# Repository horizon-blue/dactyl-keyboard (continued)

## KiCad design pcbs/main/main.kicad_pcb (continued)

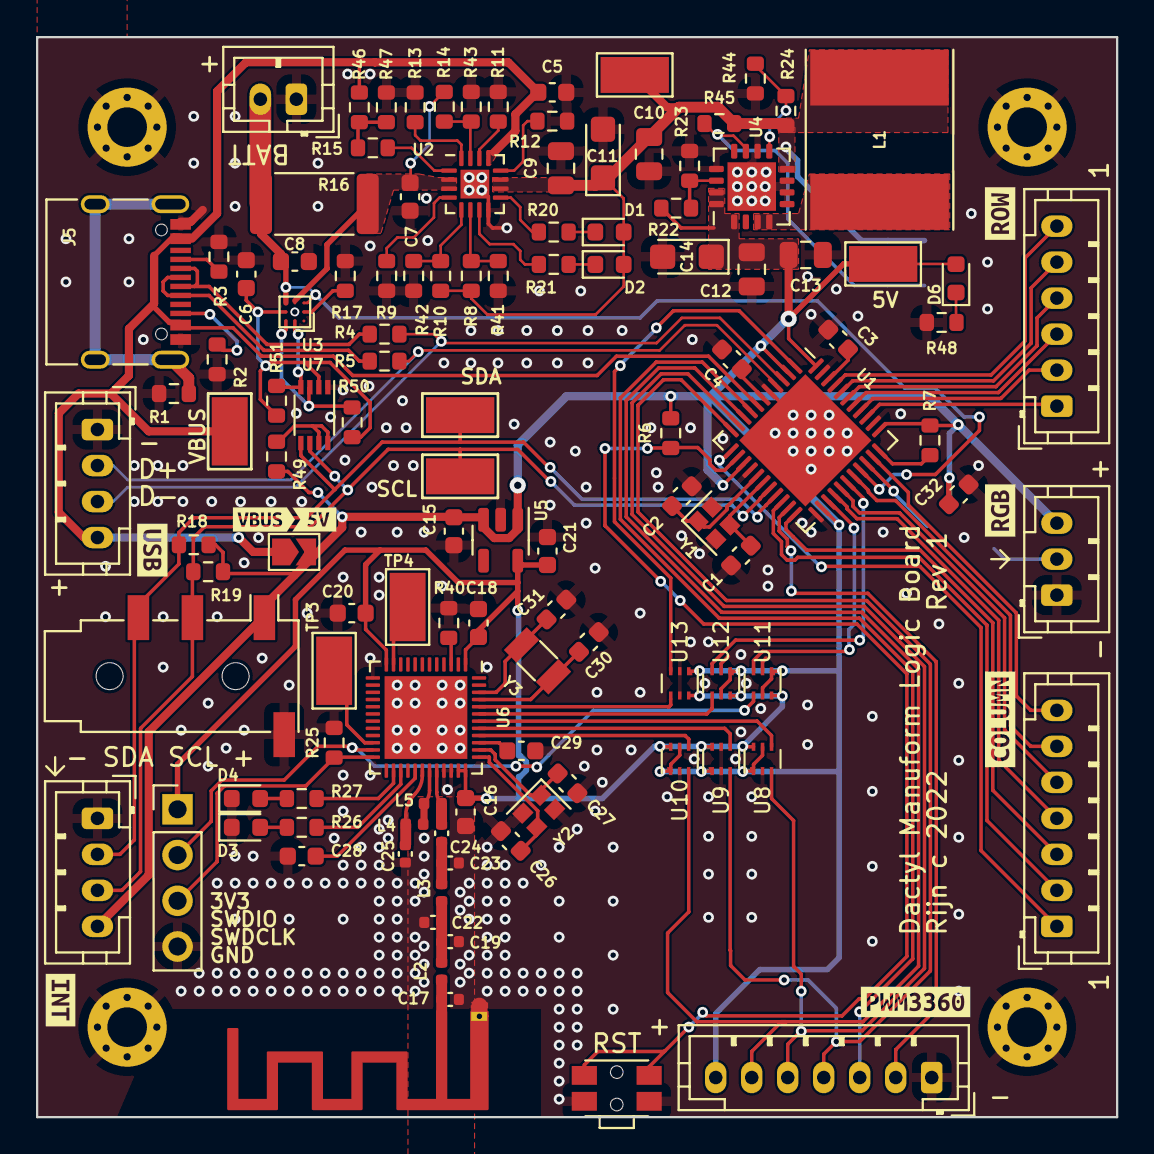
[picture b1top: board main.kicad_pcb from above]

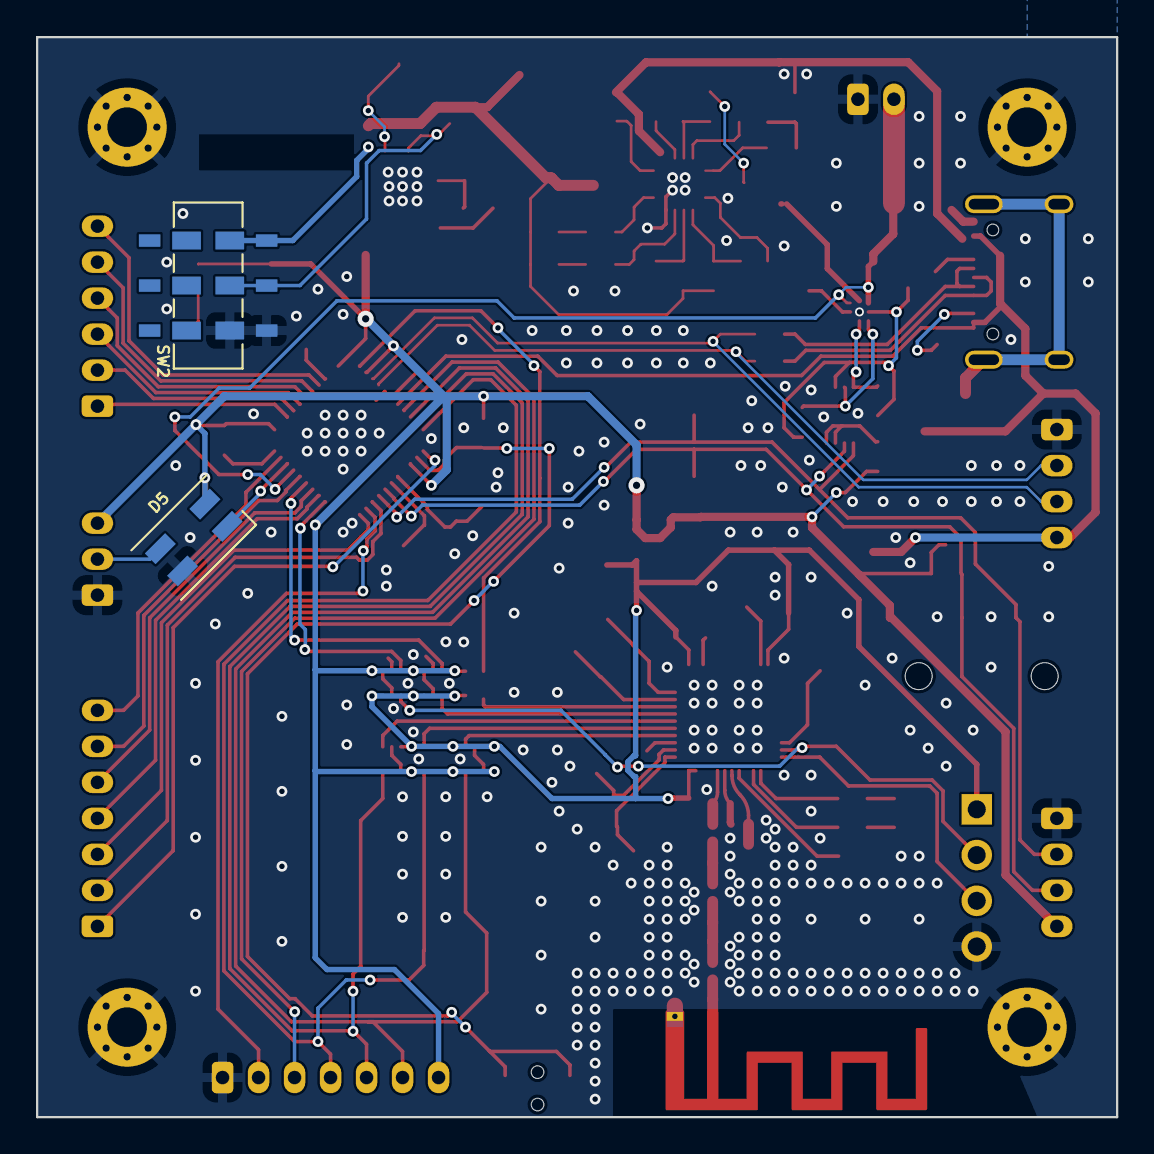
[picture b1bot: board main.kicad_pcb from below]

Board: 2 copper layers, 60.0 x 60.0 mm, 131 parts (2 on the bottom side), 94 nets.

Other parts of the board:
kibuzzard-62C9005A: G***; kibuzzard-62C9005A
kibuzzard-62C9006A: G***; kibuzzard-62C9006A
kibuzzard-62C9009F: G***; kibuzzard-62C9009F
kibuzzard-62C90078: G***; kibuzzard-62C90078
kibuzzard-62C90085: G***; kibuzzard-62C90085
kibuzzard-62C90092: G***; kibuzzard-62C90092
kibuzzard-62F083BB: G***; kibuzzard-62F083BB
kibuzzard-62F083D5: G***; kibuzzard-62F083D5

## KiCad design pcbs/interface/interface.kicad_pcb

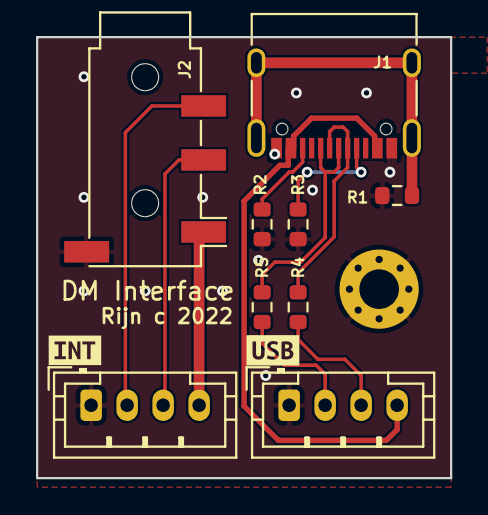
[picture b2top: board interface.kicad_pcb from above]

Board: 4 copper layers, 23.0 x 24.5 mm, 12 parts (0 on the bottom side), 12 nets.

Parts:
H1: MountingHole_Pad; MountingHole_2.2mm_M2_Pad_Via
J1: USB_C_Receptacle_USB2.0; USB_C_Receptacle_XKB_U262-16XN-4BVC11
J2: AudioJack4_Ground; Jack_3.5mm_PJ320D_Horizontal
J3, J4: Conn_01x04_Female; JST_PH_B4B-PH-K_1x04_P2.00mm_Vertical
R1: 0; R_0603_1608Metric
R2, R3: 5.1K; R_0603_1608Metric
R4, R5: 22; R_0603_1608Metric
kibuzzard-62C8FF7E: G***; kibuzzard-62C8FF7E
kibuzzard-62C8FF78: G***; kibuzzard-62C8FF78

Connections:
+5V: J2.T, J3.4
/D+: J4.2, R5.2
/D-: J4.3, R4.2
/SCL: J2.R1, J3.3
/SDA: J2.R2, J3.2
GND: H1.1, J1.A1 (GND), J1.A12 (GND), J1.B1 (GND), J1.B12 (GND), J2.S, J3.1, J4.1, R1.2, R2.1, R3.1
unnamed: J1.A5 (CC1), R3.2
unnamed: J1.A6 (D+), J1.B6 (D+), R5.1
unnamed: J1.A7 (D-), J1.B7 (D-), R4.1
unnamed: J1.B5 (CC2), R2.2
unnamed: J1.S1 (SHIELD), R1.1
VBUS: J1.A4 (VBUS), J1.A9 (VBUS), J1.B4 (VBUS), J1.B9 (VBUS), J4.4

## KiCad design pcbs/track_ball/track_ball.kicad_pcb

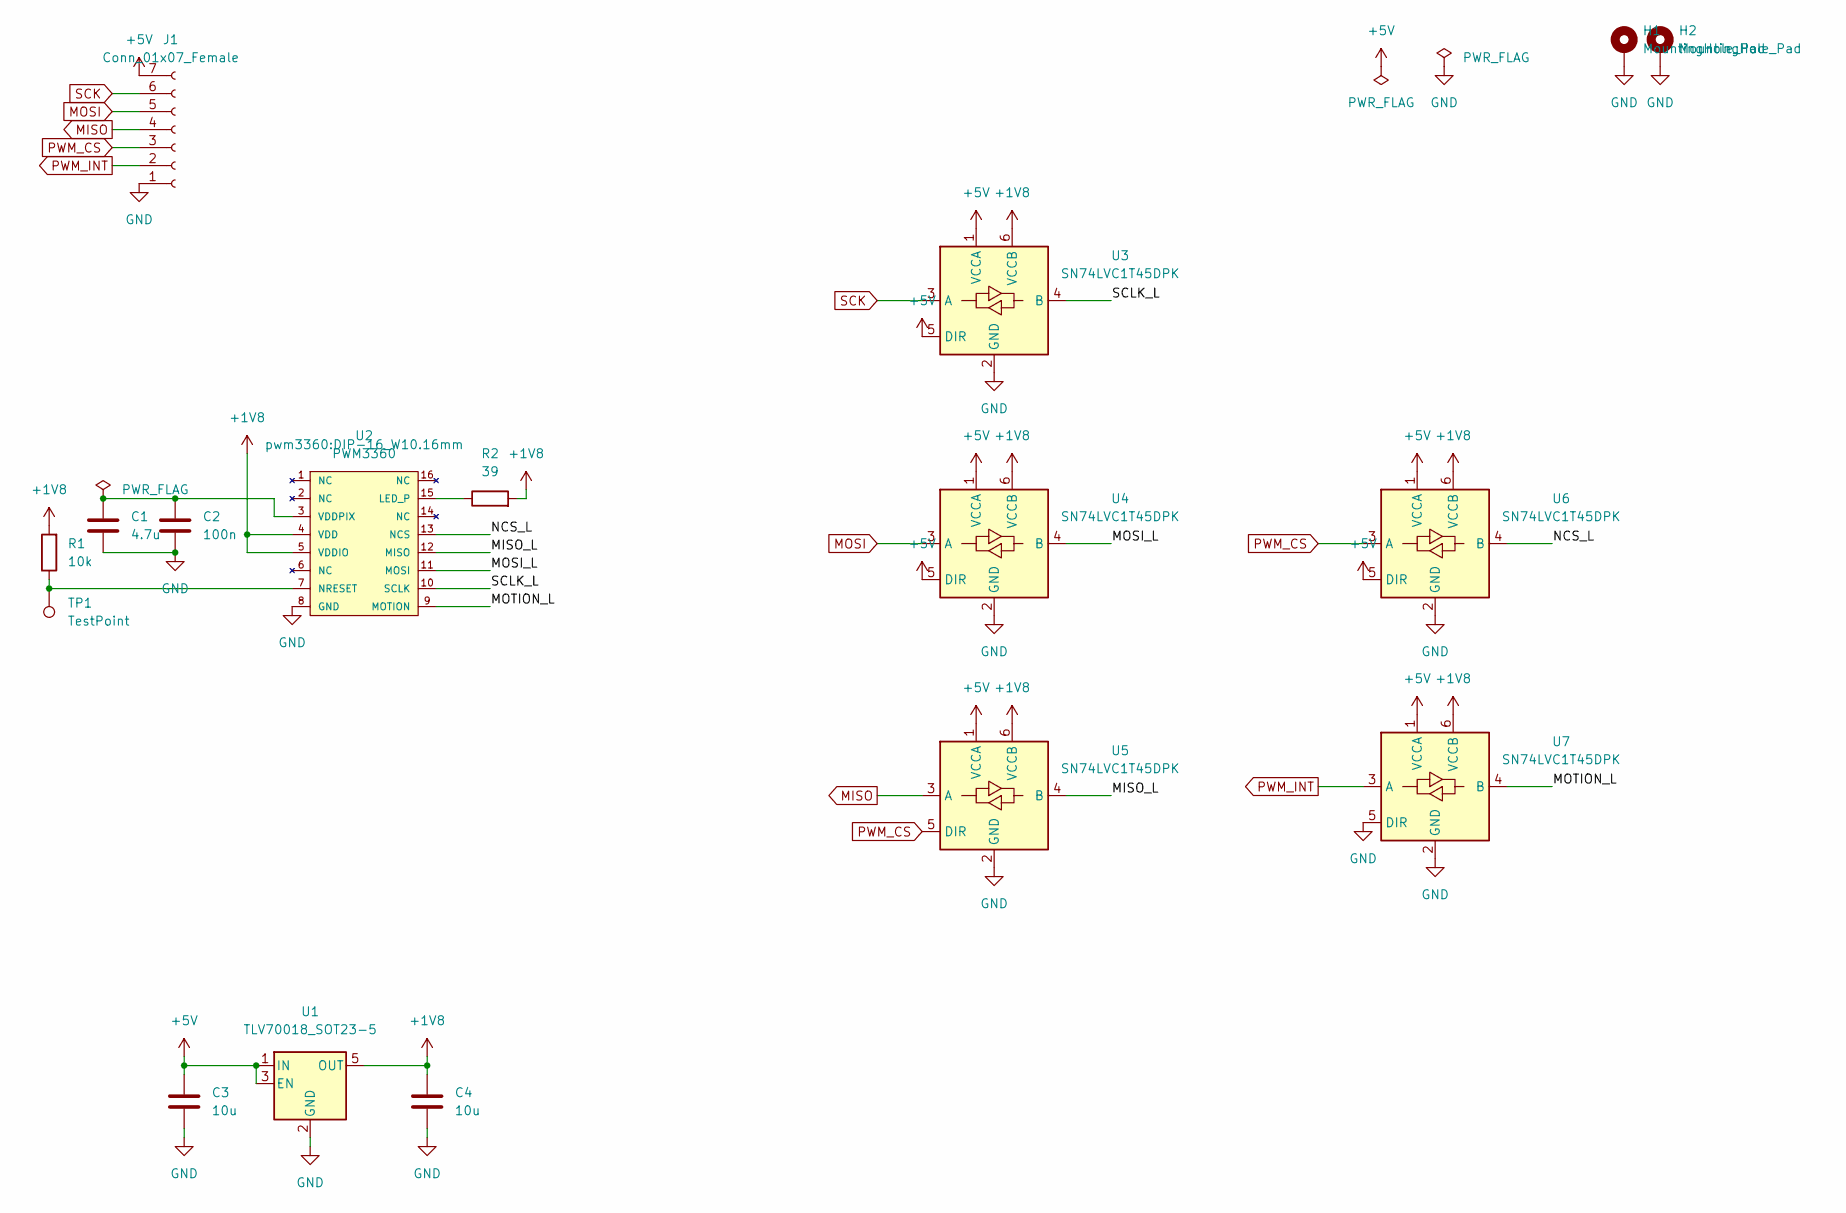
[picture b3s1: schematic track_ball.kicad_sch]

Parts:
C1: 4.7u; C_0603_1608Metric
C2: 100n; C_0603_1608Metric
C3, C4: 10u; C_0603_1608Metric
H1, H2: MountingHole_Pad; MountingHole_2.2mm_M2_Pad_Via
J1: Conn_01x07_Female; JST_PH_B7B-PH-K_1x07_P2.00mm_Vertical
R1: 10k; R_0603_1608Metric
R2: 39; R_0603_1608Metric
TP1: TestPoint; TestPoint_Pad_D1.5mm
U1: TLV70018_SOT23-5; SOT-23-5
U2: PWM3360; DIP-16_W10.16mm
U3, U4, U5, U6, U7: SN74LVC1T45DPK; USON-6

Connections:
+1V8: C4.1, R1.2, R2.2, U1.5 (OUT), U2.4 (VDD), U2.5 (VDDIO), U3.6 (VCCB), U4.6 (VCCB), U5.6 (VCCB), U6.6 (VCCB), U7.6 (VCCB)
+5V: C3.1, J1.7, U1.1 (IN), U1.3 (EN), U3.1 (VCCA), U3.5 (DIR), U4.1 (VCCA), U4.5 (DIR), U5.1 (VCCA), U6.1 (VCCA), U6.5 (DIR), U7.1 (VCCA)
/MISO_L: U2.12 (MISO), U5.4 (B)
/MOSI_L: U2.11 (MOSI), U4.4 (B)
/MOTION_L: U2.9 (MOTION), U7.4 (B)
/NCS_L: U2.13 (NCS), U6.4 (B)
/SCLK_L: U2.10 (SCLK), U3.4 (B)
GND: C1.2, C2.2, C3.2, C4.2, H1.1, H2.1, J1.1, U1.2 (GND), U2.8 (GND), U3.2 (GND), U4.2 (GND), U5.2 (GND), U6.2 (GND), U7.2 (GND), U7.5 (DIR)
MISO: J1.4, U5.3 (A)
MOSI: J1.5, U4.3 (A)
unnamed: C1.1, C2.1, U2.3 (VDDPIX)
unnamed: R1.1, TP1.1, U2.7 (NRESET)
unnamed: R2.1, U2.15 (LED_P)
PWM_CS: J1.3, U5.5 (DIR), U6.3 (A)
PWM_INT: J1.2, U7.3 (A)
SCK: J1.6, U3.3 (A)

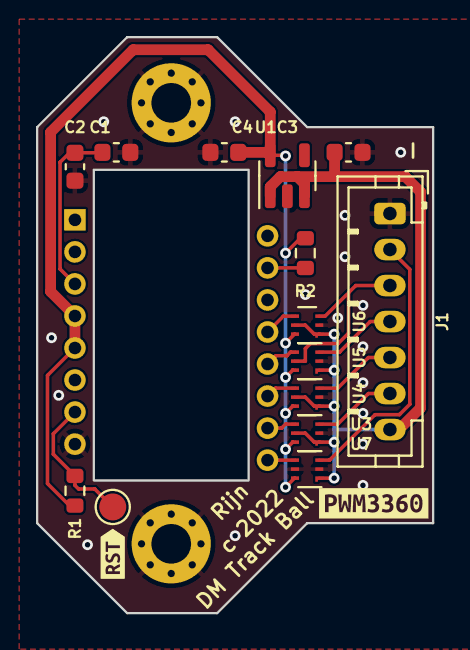
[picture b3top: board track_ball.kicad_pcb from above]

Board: 4 copper layers, 22.0 x 32.0 mm, 19 parts (0 on the bottom side), 16 nets.

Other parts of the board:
kibuzzard-62C9E1CF: G***; kibuzzard-62C9E1CF
kibuzzard-62C9E26A: G***; kibuzzard-62C9E26A

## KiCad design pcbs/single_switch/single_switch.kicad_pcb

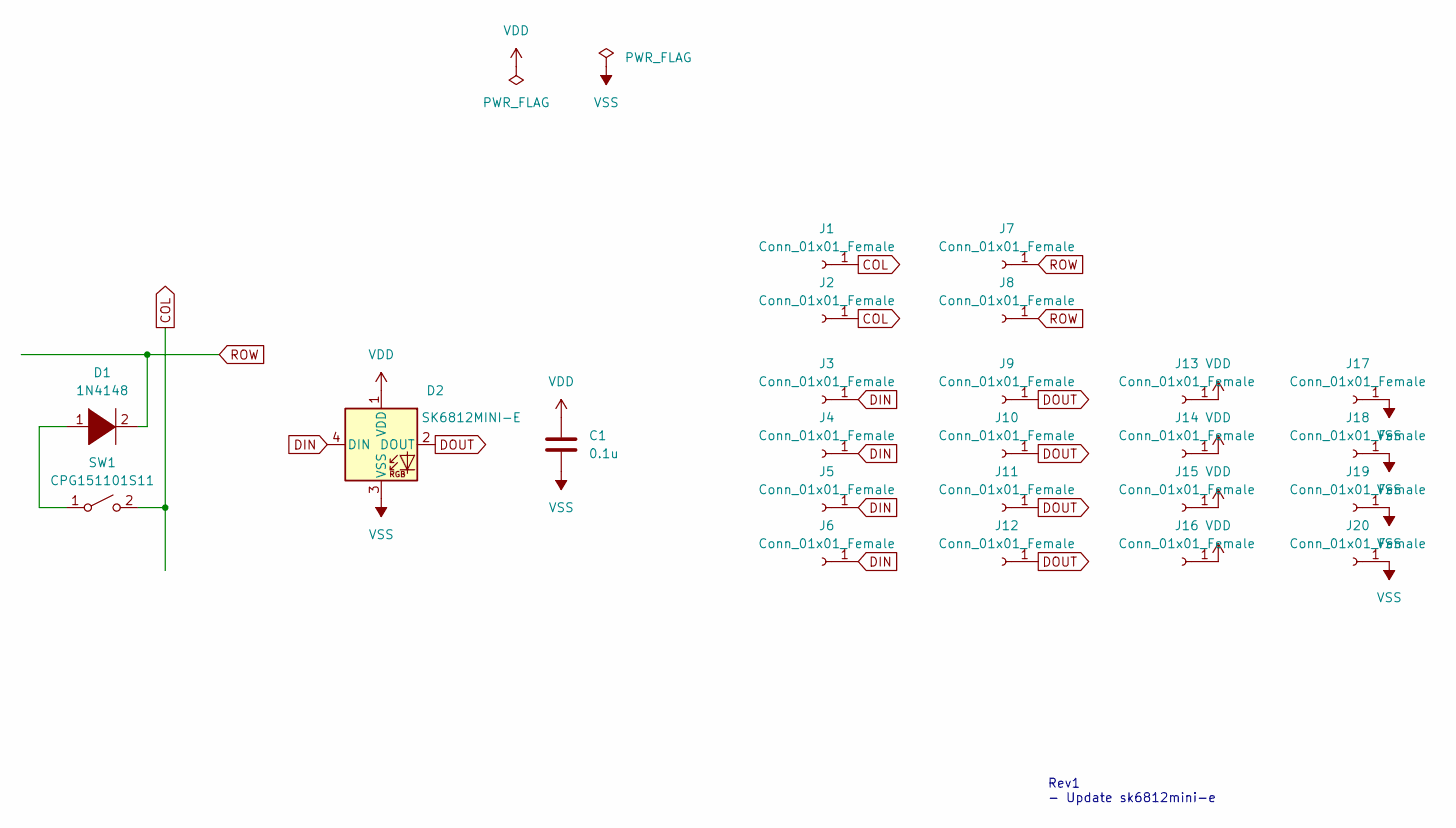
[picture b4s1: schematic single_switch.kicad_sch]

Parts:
C1: 0.1u; C_0603_1608Metric
D1: 1N4148; D_SOD-123
D2: SK6812MINI-E; MX_SK6812MINI-E_REV
J1, J2, J3, J4, J5, J6, J7, J8, J9, J10, J11, J12, J13, J14, J15, J16, J17, J18, J19, J20: Conn_01x01_Female; PinSocket_1x01_P2.00mm_Vertical
SW1: CPG151101S11; Kailh_MX_Socket

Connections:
COL: J1.1, J2.1, SW1.2 (B)
DIN: D2.4 (DIN), J3.1, J4.1, J5.1, J6.1
DOUT: D2.2 (DOUT), J9.1, J10.1, J11.1, J12.1
unnamed: D1.1 (K), SW1.1 (A)
ROW: D1.2 (A), J7.1, J8.1
VDD: C1.1, D2.1 (VDD), J13.1, J14.1, J15.1, J16.1
VSS: C1.2, D2.3 (VSS), J17.1, J18.1, J19.1, J20.1

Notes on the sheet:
Rev1 - Update sk6812mini-e

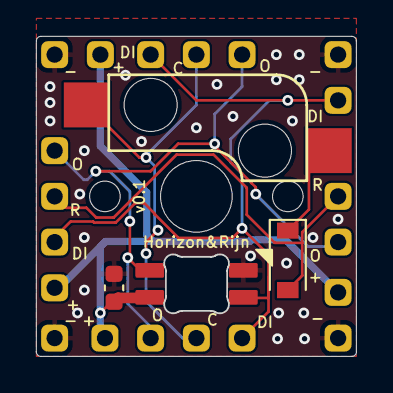
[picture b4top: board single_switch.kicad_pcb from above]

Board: 4 copper layers, 17.8 x 17.8 mm, 24 parts (1 on the bottom side), 7 nets.

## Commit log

2021-10-21 brad_dolph changes
2021-10-22 In the ballpark for customer
2021-10-28 Column tweaking
2021-11-06 Moving workflow setup out of general repo
2021-11-21 Filename fix
2021-11-22 Wilder cluster tweaks, needs more work, smoothing, connect to walls not just corners of key holes.
    Added --save_path argument to customize save paths on local system without dirtying json with local paths.
2021-11-26 Cylinders present for each keyhole
2021-11-30 Initial support branching test
2021-12-01 Supports in a ballpark and exporting separately for right side.
2021-12-08 About to connect supports and expand support plates
2021-12-09 Testing issues with cadquery
2021-12-09 Another test
2021-12-09 Global clean = false on union
2021-12-09 Returning clean=False in bits
2021-12-10 Almost working
2021-12-10 Basic posts and plates working well
2021-12-10 Testing print 1
2021-12-12 Pointy supports
2022-02-22 Tweaks towards new polydactyl
2022-02-23 Trackball BTU testing
2022-02-23 Added new hot swap resources
2022-02-24 Bottom base shell back in render
2022-02-24 Recent bits
    Recent bits
2022-02-25 removed supports for new BTU trackball
2022-02-27 Playing with BTU trackball
2022-02-28 Tests
2022-03-02 it fits!
2022-03-05 Moved minithicc screw hole back inside
2022-03-05 Tweaks to screw placement and thumb cluster height.
2022-03-06 Adding fourth key to cluster, looks good, just needs moving forward (and the keyhole actually cutting...)
2022-03-06 Fourth key looking good. Moved cluster forward and out.
2022-03-07 Tighter angle on top row keys
2022-03-09 Odd bug fix and tighter OLED walls
2022-03-16 Added minithicc3.py for 3-key cluster arc.
2022-04-03 New trackball files
2022-04-03 Updated for BTU
2022-04-10 On the path to separate socket
2022-04-14 BTU in the ball transfer park
2022-04-22 Removed stale assets and added new trackball socket assets
2022-04-24 Moved trackball cluster out by 4mm to accommodate top key placement
2022-04-26 Logo import and placement working
2022-04-28 Not bad
2022-04-29 Key moved, trackball cluster walls reworked
2022-04-29 Back to derek_hotswap
2022-05-21 Shifted columns and cluster
2022-05-23 Big trackball in wall, fixed cluster walls, tilted trackball and trimmed wide wall
2022-05-24 Testing PR of trackball generator function
2022-05-24 Fixed issues
2022-05-25 Edited "air" to gap
2022-05-26 Thickened walls
2022-05-26 Hacked thicker rear wall
2022-05-26 Sensible place to plateau for now
2022-05-28 Attempting modular bearing tracball generator
2022-05-29 cadquery play
2022-05-31 Cluster checks fixed
2022-06-03 playing with bearing fins
2022-06-04 adding lip to socket
2022-06-05 Still working on lip height...
2022-06-05 Lip looking good
2022-06-07 Not a bad spot
2022-06-30 Remove posts under trackball for Wylderbuilds's thumb cluster
2022-06-30 Remove unused YAML config file
2022-06-30 newline at the end of file
2022-07-01 Hacking the cluster
2022-07-01 Update screw locations & walls
2022-07-01 Using Loligagger's config
    Reference: https://geekhack.org/index.php?topic=88576.msg2696694#msg2696694
2022-07-01 Sort of fix the trackball for Loligagger's layout
2022-07-01 Fix the artifacts on thumb cluster connection
2022-07-01 Adding STL files
2022-07-01 Crop image
2022-07-01 Remove unrelated files
2022-07-02 Remove "+" from file name
2022-08-09 Modify carbonfet's thumbcluster to fit ergodox layout
2022-08-09 Fix pinky 1.5u keycaps rendering logic
2022-08-09 fix walls and connections for pinky 1.5u
2022-08-10 Fix valid-key logic
2022-08-10 Updated screw location
2022-08-23 Fix the screw hole position on the last column
2022-09-01 Temporarily check in stl with carbonfet thumbclusters
2022-09-01 Update screw size so it supports M3x6 screws
2022-09-01 Adding PCB screws
2022-09-02 Adding pcb screw inserts to config
2022-09-02 Making PCB screw inserts optional
2022-09-10 Try generating wrist rest
2022-09-27 Adding STLs for base plate with PCB screw inserts (for our customized PCB)
2022-09-27 STL for TRRS and Type C interface
2022-09-27 PCB files
